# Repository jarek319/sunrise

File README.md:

# sunrise
An OLED driver that simulates the rising sun

I got my hands on an OLED panel, and wanted to use it to simulate the rising sun, similar to those sunrise alarm clocks that use a high powered LED and gradually increase its brightness as approaches your wake up time.

The dimensions of the panel allowed me to easily stick it right above me. It works great, but gets a little warm, need to check out other ways of controlling the constant current device.

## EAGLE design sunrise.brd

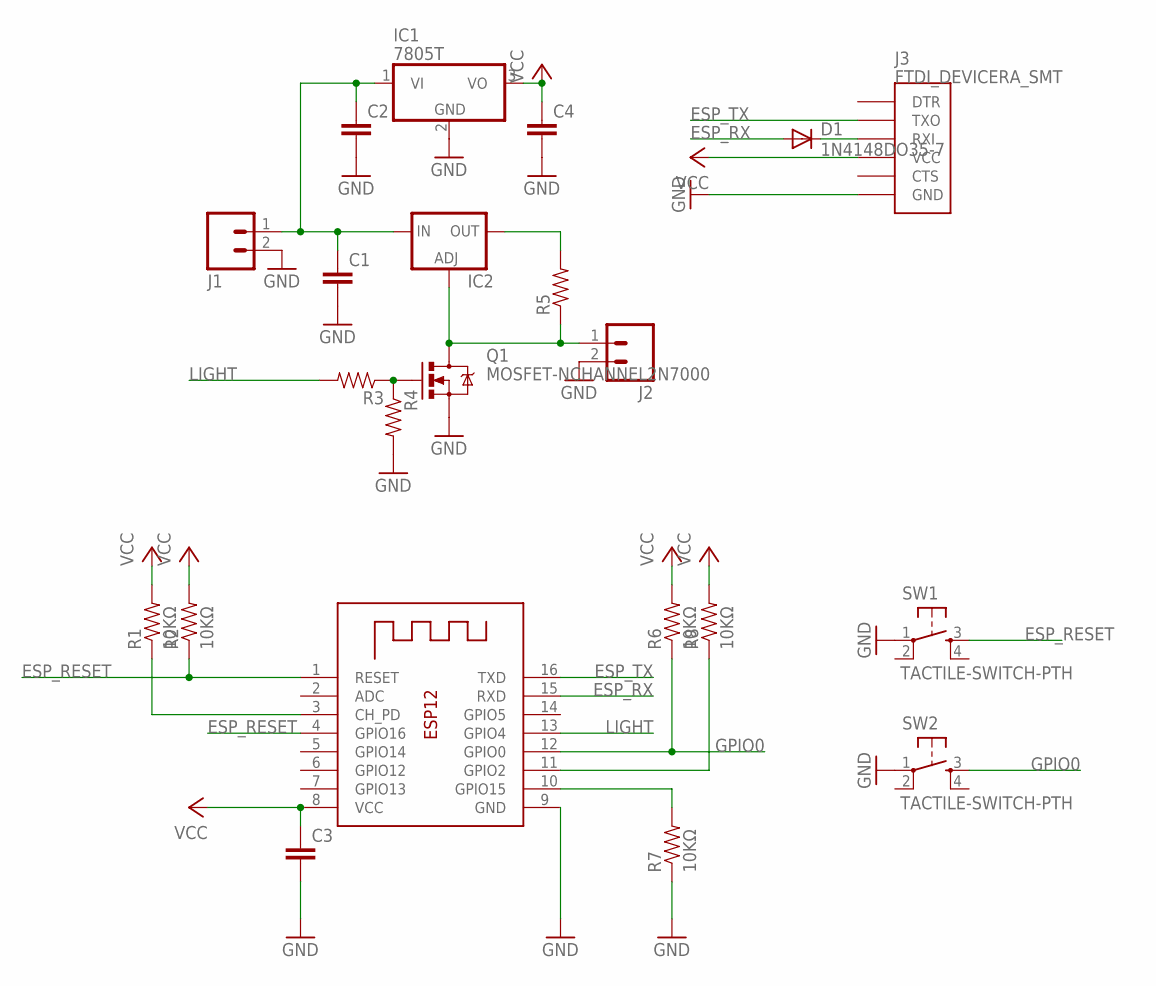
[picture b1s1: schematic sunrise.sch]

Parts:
C1, C2, C3, C4: 0.1UF-50V-20%(PTH)KIT-EZ; CAP-PTH-SMALL-KIT
D1: 1N4148DO35-7; DO35-7
IC1: 7805T; TO220H
IC2: LM317-TO3; TO3-K02
J1, J2: M02LOCK_LONGPADS; 1X02_LOCK_LONGPADS
J3: FTDI_DEVICERA_SMT; FTDI_DEVICE_RA_SMT
Q1: MOSFET-NCHANNEL2N7000; TO-92
R1, R2, R6, R7, R8: 10KΩ; AXIAL-0.4
R3, R4: RESISTORPTH-1/4W; AXIAL-0.4
R5: RESISTORPTH-1W; AXIAL-0.6
SW1, SW2: TACTILE-SWITCH-PTH; TAC-SWITCH-PTH
X1: ESP-12e; ESP-12

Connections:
!CS: R7.P$2 (2), X1.10 (GPIO15)
!D/C: R8.P$1 (1), X1.11 (GPIO2)
ESP_RESET: R2.P$1 (1), SW1.3, X1.1 (RESET), X1.4 (GPIO16)
ESP_RX: D1.A, X1.15 (RXD)
ESP_TX: J3.2 (TXO), X1.16 (TXD)
GND: C1.2, C2.2, C3.2, C4.2, IC1.2 (GND), J1.2, J2.2, J3.6 (GND), Q1.1 (S), R4.P$2 (2), R7.P$1 (1), SW1.1, SW2.1, X1.9 (GND)
GPIO0: R6.P$1 (1), SW2.3, X1.12 (GPIO0)
LIGHT: R3.P$2 (2), X1.13 (GPIO4)
unnamed: C1.1, C2.1, IC1.1 (VI), IC2.1 (IN), J1.1
unnamed: IC2.3 (OUT), R5.P$2 (2)
unnamed: IC2.2 (ADJ), J2.1, Q1.3 (D), R5.P$1 (1)
unnamed: Q1.2 (G), R3.P$1 (1), R4.P$1 (1)
unnamed: D1.C, J3.3 (RXI)
unnamed: R1.P$1 (1), X1.3 (CH_PD)
VCC: C3.1, C4.1, IC1.3 (VO), J3.4 (VCC), R1.P$2 (2), R2.P$2 (2), R6.P$2 (2), R8.P$2 (2), X1.8 (VCC)

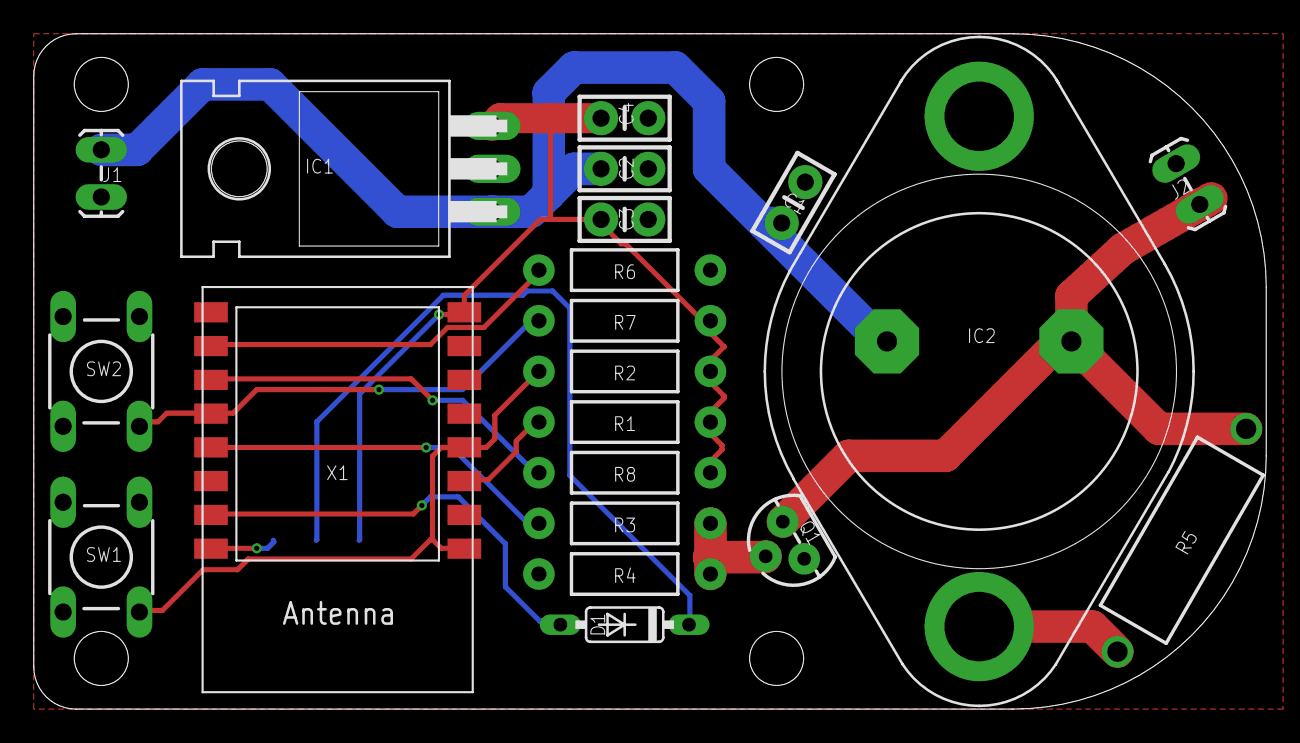
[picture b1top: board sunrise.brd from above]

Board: 2 copper layers, 73.0 x 40.0 mm, 22 parts (1 on the bottom side), 15 nets.

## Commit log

2018-07-05 design tested: working but needs tweaks

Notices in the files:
parts and their libraries:
SparkFun-Capacitors: Licensing: Creative Commons ShareAlike 4.0 International - https://creativecommons.org/licenses/by-sa/4.0
